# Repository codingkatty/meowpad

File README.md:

# meowpad
this is a macropad made for [hackpad](https://hackpad.hackclub.com/) / [highway](https://highway.hackclub.com/)! i followed the guide in hackpad to make the macropad. the macropad features 4 keys to type, an oled and a neopixel. the keys are for wasd because apparently i don't have much ideas, may as well use it for gaming!

### from pcb
here are the schematic and pcb pictures, this is the first time i used kicad and it was really easy to use, esspecially with the help of the guide.

### to case
i made the case in fusion360, it was my first time using it and i was pretty slow, took pretty long ~4 hours (at least longer than i expected it to take). there's a little translucent part for the neopixel, not sure exactly how would i make it tho i plan to print it with my translucent purple filament.

### and code
i have modified the code in the guide and added a few stuff for neopixel and the oled. for some, I wasn't able to find some answers online so I think I will fix it when i maybe get it. Right now the code written is really simple, what it (is supposed to do) does is to type wasd, neopixel shows purple and oled is a rainbow coloured (highway reference :3) cat thing that changes when typing.

(i hope it works / i may or may not need to rotate the image)

> checkout `firmware/test.py` for what i want to make for the oled, (you can run it on your pc!)

### (& bom)
- Seeed XIAO RP2040 - x1
- MX-Style switches - x4
- 0.91 inch OLED displays - x1
- Blank DSA keycaps (White) - x4
- SK6812 MINI-E LEDs - x1
- M3x16mm screws - x6
- M3x5mx4mm heatset inserts - x6

---
in the future when its built imma tinker around with it- i'll try to make it able to type! hehe

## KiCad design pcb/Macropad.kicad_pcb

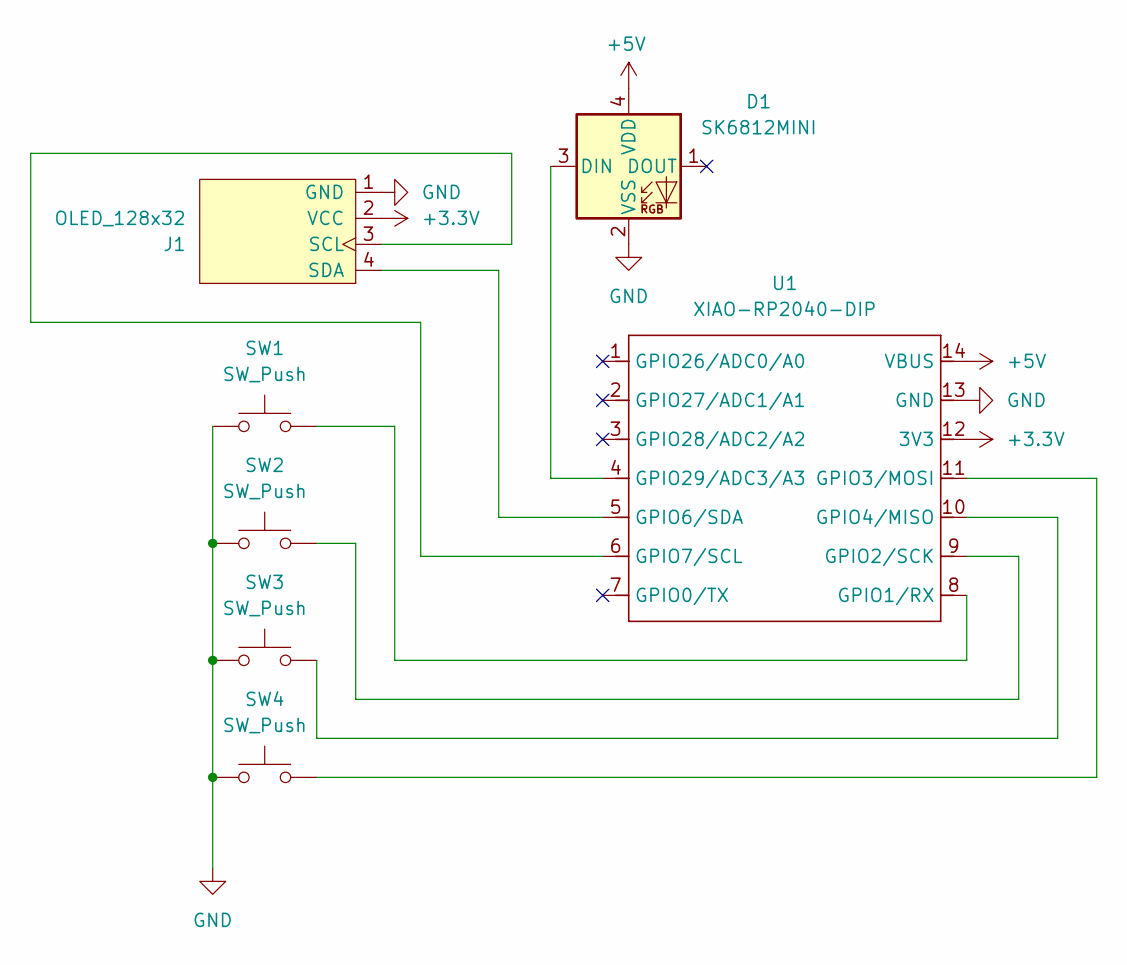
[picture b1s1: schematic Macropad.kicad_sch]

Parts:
D1: SK6812MINI; LED_SK6812MINI_PLCC4_3.5x3.5mm_P1.75mm
J1: OLED_128x32; SSD1306-0.91-OLED-4pin-128x32
SW1, SW2, SW3, SW4: SW_Push; SW_Cherry_MX_1.00u_PCB
U1: XIAO-RP2040-DIP

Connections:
+3.3V: J1.2 (VCC), U1.12 (3V3)
+5V: D1.4 (VDD), U1.14 (VBUS)
GND: D1.2 (VSS), J1.1 (GND), SW1.1, SW2.1, SW3.1, SW4.1, U1.13 (GND)
unnamed: D1.3 (DIN), U1.4 (GPIO29/ADC3/A3)
unnamed: J1.3 (SCL), U1.6 (GPIO7/SCL)
unnamed: J1.4 (SDA), U1.5 (GPIO6/SDA)
unnamed: SW1.2, U1.8 (GPIO1/RX)
unnamed: SW2.2, U1.9 (GPIO2/SCK)
unnamed: SW4.2, U1.11 (GPIO3/MOSI)
unnamed: SW3.2, U1.10 (GPIO4/MISO)

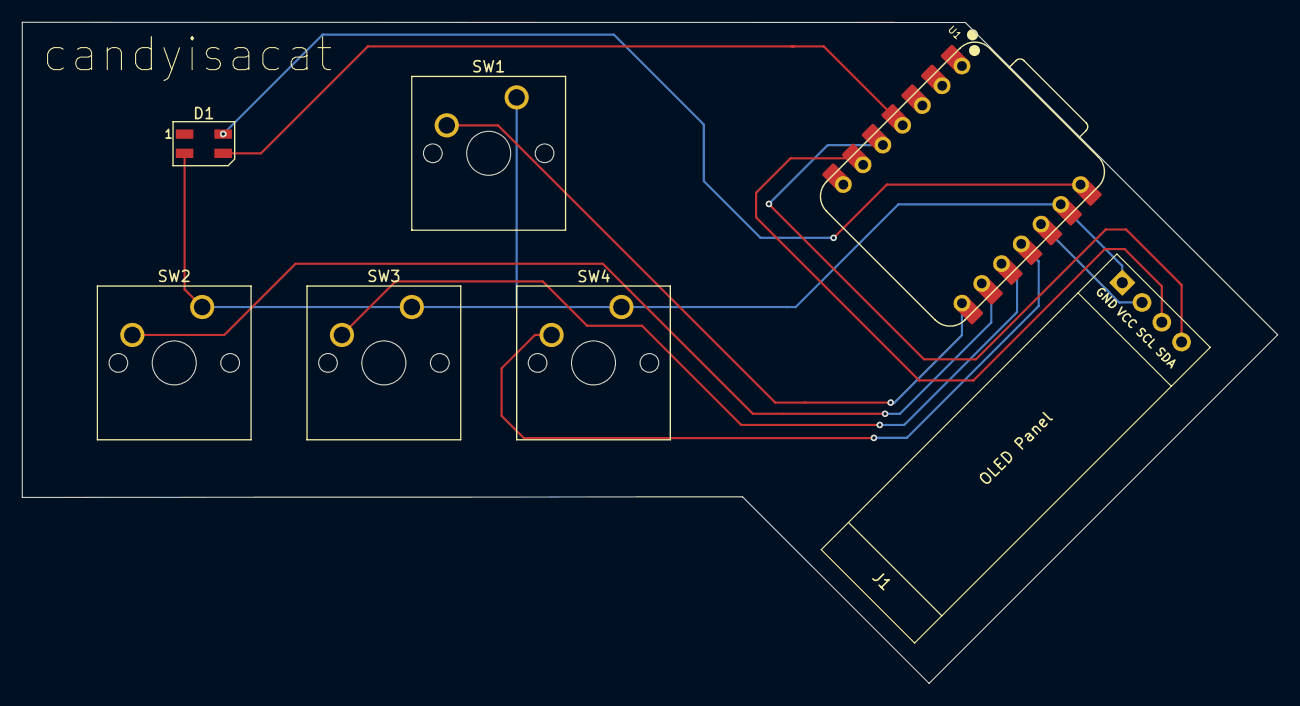
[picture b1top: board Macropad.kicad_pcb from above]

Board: 2 copper layers, 114.1 x 60.1 mm, 7 parts (0 on the bottom side), 10 nets.

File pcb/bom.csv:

"Id";"Designator";"Footprint";"Quantity";"Designation";"Supplier and ref";
1;"D1";"LED_SK6812MINI_PLCC4_3.5x3.5mm_P1.75mm";1;"SK6812MINI";;;
2;"J1";"SSD1306-0.91-OLED-4pin-128x32";1;"OLED_128x32";;;
3;"SW2,SW4,SW1,SW3";"SW_Cherry_MX_1.00u_PCB";4;"SW_Push";;;
4;"U1";"XIAO-RP2040-DIP";1;"XIAO-RP2040-DIP";;;

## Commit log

2025-06-05 meowpad! :3
2025-06-10 adddddd
2025-06-10 add production
